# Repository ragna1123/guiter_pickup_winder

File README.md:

# ピックアップ製造計画

## ワインダー

## ピックアップボビン&カバー

### ラインナップ

- TELECASTER
- JAZZMASTER
- P90

### 実装予定

- A90
- STRATCASTER

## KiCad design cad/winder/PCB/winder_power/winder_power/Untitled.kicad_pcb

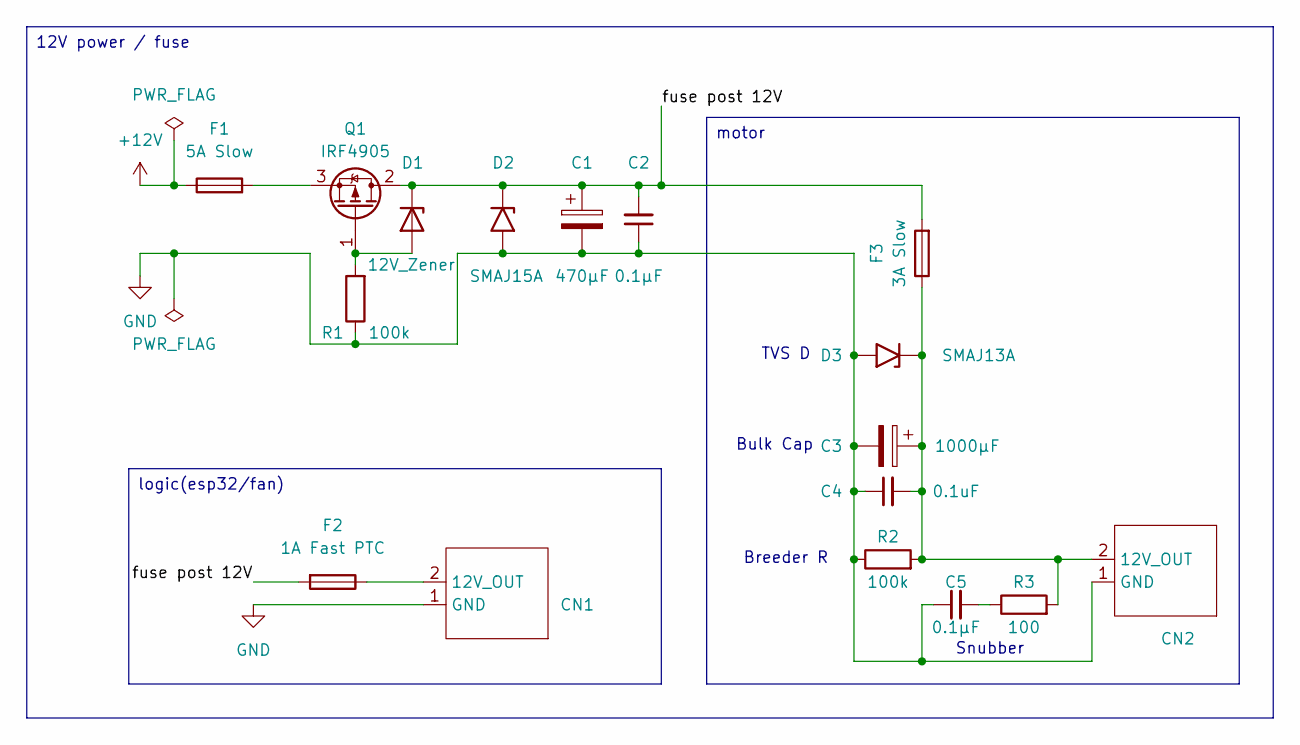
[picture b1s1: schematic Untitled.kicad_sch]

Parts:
C1: 470µF; CP_Radial_D10.0mm_P5.00mm
C2, C5: 0.1µF; C_1206_3216Metric_Pad1.33x1.80mm_HandSolder
C3: 1000µF; CP_Radial_D13.0mm_P5.00mm
C4: 0.1uF; C_1206_3216Metric_Pad1.33x1.80mm_HandSolder
CN1: JST_XH_B2B-XH-AM_1x02_P2.50mm_Vertical
CN2: JST_VH_B2P-VH-B_1x02_P3.96mm_Vertical
D1: 12V_Zener; TSOT-23_HandSoldering
D2: SMAJ15A; D_SMA
D3: SMAJ13A; D_SMA
F1: 5A Slow; FuseHolder_Blade_ATO_Littelfuse_FLR_178.6165
F2: 1A Fast PTC; Fuse_Bourns_MF-RHT070
F3: 3A Slow; FuseHolder_Blade_ATO_Littelfuse_FLR_178.6165
Q1: IRF4905; TO-220-3_Vertical
R1, R2: 100k; R_1206_3216Metric_Pad1.30x1.75mm_HandSolder
R3: 100; R_1206_3216Metric_Pad1.30x1.75mm_HandSolder

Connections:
+12V: F1.1; also elsewhere on the board
/fuse post 12V: C1.1, C2.2, D1.1 (K), D2.1 (A1), F2.2, F3.2, Q1.2 (D)
GND: C1.2, C2.1, C3.2, C4.1, C5.1, CN1.1 (GND), CN2.1 (GND), D2.2 (A2), D3.2 (A2), R1.1, R2.1; also elsewhere on the board
unnamed: C5.2, R3.1
unnamed: CN1.2 (12V_OUT), F2.1
unnamed: C3.1, C4.2, CN2.2 (12V_OUT), D3.1 (A1), F3.1, R2.2, R3.2
unnamed: D1.2 (A), Q1.1 (G), R1.2
unnamed: F1.2, Q1.3 (S)

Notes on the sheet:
Bulk Cap
Breeder R
TVS D
Snubber
logic(esp32/fan)
12V power / fuse
motor

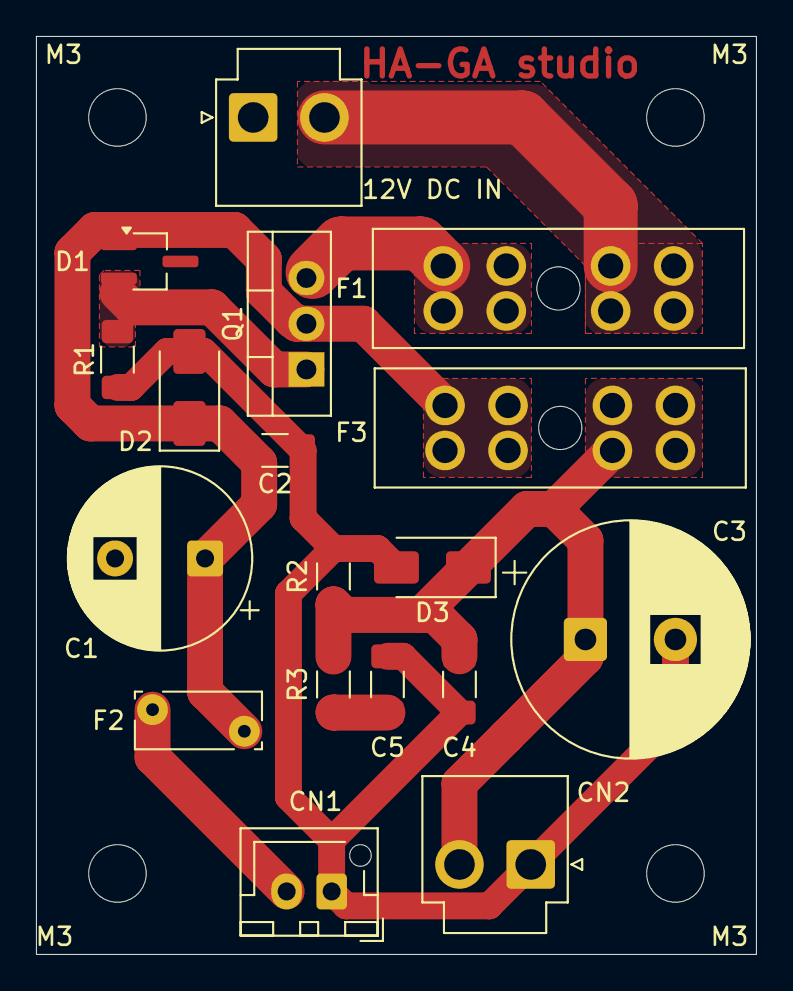
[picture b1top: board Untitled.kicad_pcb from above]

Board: 2 copper layers, 40.0 x 51.0 mm, 22 parts (0 on the bottom side), 8 nets.

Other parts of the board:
12V DC IN: JST_VH_B2P-VH-B_1x02_P3.96mm_Vertical
M3, M3#2, M3#3, M3#4: MountingHole_3.2mm_M3

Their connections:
+12V: 12V DC IN.2; also elsewhere on the board
GND: 12V DC IN.1; also elsewhere on the board

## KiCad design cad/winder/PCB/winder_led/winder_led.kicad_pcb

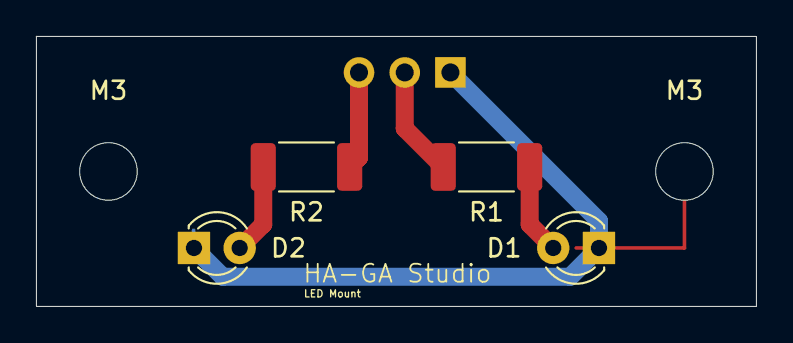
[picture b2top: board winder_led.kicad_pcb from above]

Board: 2 copper layers, 40.0 x 15.0 mm, 7 parts (1 on the bottom side), 5 nets.

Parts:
D1, D2: LED; LED_D3.0mm_FlatTop
J1: PinHeader_1x03_P2.54mm_Vertical
M3, M3#2: MountingHole_3.2mm_M3
R1, R2: R_Small; R_2010_5025Metric_Pad1.40x2.65mm_HandSolder

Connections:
/GPIO4: J1.2, R1.1
/GPIO5: J1.3, R2.1
GND: D1.1 (K), D2.1 (K), J1.1
unnamed: D1.2 (A), R1.2
unnamed: D2.2 (A), R2.2

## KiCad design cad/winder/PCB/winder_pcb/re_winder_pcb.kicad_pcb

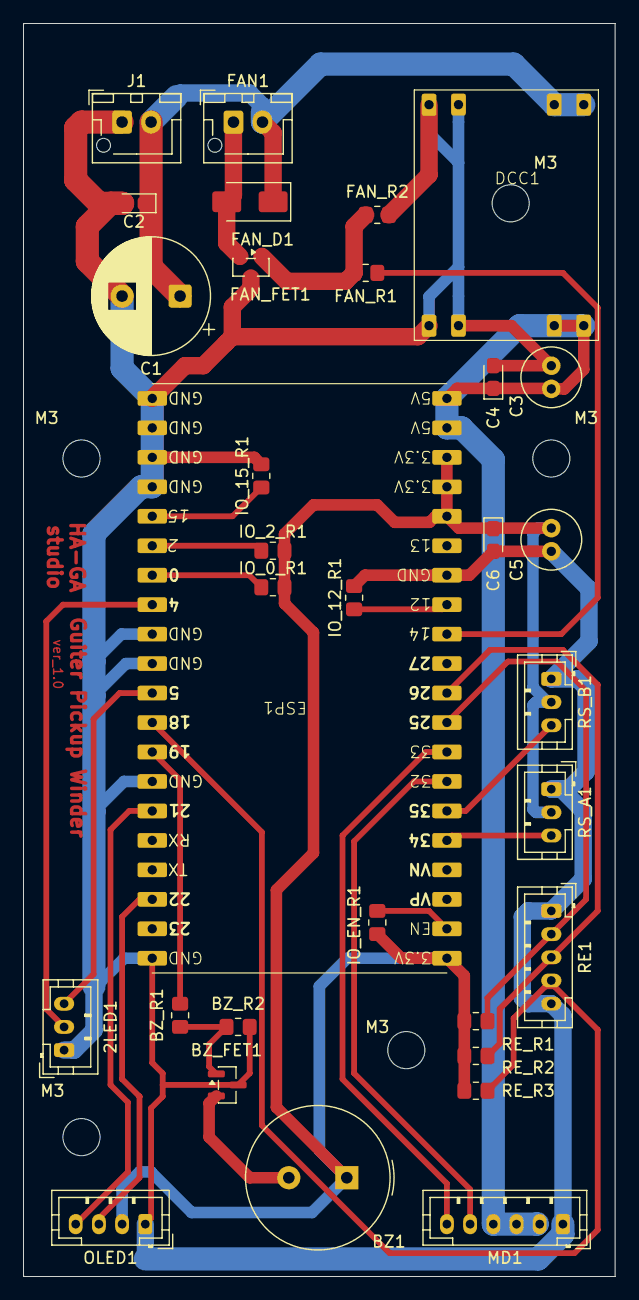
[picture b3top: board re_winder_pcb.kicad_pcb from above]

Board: 2 copper layers, 51.0 x 108.0 mm, 37 parts (0 on the bottom side), 26 nets.

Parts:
2LED1: LED; JST_PH_B3B-PH-K_1x03_P2.00mm_Vertical
BZ1: Buzzer; Buzzer_TDK_PS1240P02BT_D12.2mm_H6.5mm
BZ_FET1: AO3400A; SOT-23
BZ_R1: 100_R; R_0805_2012Metric_Pad1.20x1.40mm_HandSolder
BZ_R2: 100K_R; R_0805_2012Metric_Pad1.20x1.40mm_HandSolder
C1: 470uF; CP_Radial_D10.0mm_P5.00mm
C2, C4, C6: 0.1uF; CP_EIA-2012-12_Kemet-R_HandSolder
C3: 47uF; C_Radial_D5.0mm_H11.0mm_P2.00mm
C5: 10uF; C_Radial_D5.0mm_H11.0mm_P2.00mm
DCC1: DC_DW; MP1584EN_DCDC_Converter
ESP1: ESP32_Freenove_Socket
FAN1: 12V_Fan; JST_XH_B2B-XH-AM_1x02_P2.50mm_Vertical
FAN_D1: SS14; D_SMA
FAN_FET1: AO3400A; SOT-23
FAN_R1: 100_R; R_0805_2012Metric_Pad1.20x1.40mm_HandSolder
FAN_R2: 100K_R; R_0805_2012Metric_Pad1.20x1.40mm_HandSolder
IO_0_R1, IO_2_R1, IO_12_R1, IO_15_R1: 10K_R; R_0805_2012Metric_Pad1.20x1.40mm_HandSolder
IO_EN_R1: 10K_R; R_0805_2012Metric_Pad1.20x1.40mm_HandSolder
J1: 12V_IN; JST_XH_B2B-XH-AM_1x02_P2.50mm_Vertical
M3, M3#2, M3#3, M3#4, M3#5: MountingHole_3.2mm_M3
MD1: JST_PH_B6B-PH-K_1x06_P2.00mm_Vertical
OLED1: JST_PH_B4B-PH-K_1x04_P2.00mm_Vertical
RE1: RotaryEncoder_Switch; JST_PH_B5B-PH-K_1x05_P2.00mm_Vertical
RE_R1, RE_R2, RE_R3: 10K_R; R_0805_2012Metric_Pad1.20x1.40mm_HandSolder
RS_A1: JST_PH_B3B-PH-K_1x03_P2.00mm_Vertical
RS_B1: JST_PH_B3B-PH-K_1x03_P2.00mm_Vertical

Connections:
+5V: C3.1, C4.1, DCC1.4 (V_OUT+), ESP1.2 (5V), MD1.2 (VCC), MD1.3 (R_EN), MD1.4 (L_EN)
+12V: C1.1, C2.1, DCC1.2 (V_IN+), FAN1.2 (+), FAN_D1.1 (K), J1.2
/+3.3V: BZ1.1 (+), C5.1, C6.1, ESP1.3 (3.3V), IO_0_R1.2, IO_2_R1.2, IO_EN_R1.2, OLED1.2 (VCC), RE_R1.1, RE_R2.2, RE_R3.2, RS_A1.2 (VCC), RS_B1.2 (VCC)
/GPIO_4: 2LED1.2 (FW_LED), ESP1.25 (4)
/GPIO_5: 2LED1.3 (REV_LED), ESP1.24 (5)
/GPIO_14: ESP1.12 (14), FAN_R1.1
/GPIO_18: ESP1.23 (18), RE1.4 (S1), RE_R3.1
/GPIO_19: BZ_R1.2, ESP1.22 (19)
/GPIO_21: ESP1.21 (21/I2C(SDA)), OLED1.4 (SDA)
/GPIO_22: ESP1.20 (22/I2C(SCL)), OLED1.3 (SCL)
/GPIO_25: ESP1.9 (25), RE1.2 (A), RE_R1.2
/GPIO_26: ESP1.10 (26), RE1.3 (B), RE_R2.1
/GPIO_32: ESP1.7 (32), MD1.5 (R_PWM)
/GPIO_33: ESP1.8 (33), MD1.6 (L_PWM)
/GPIO_34: ESP1.5 (34), RS_A1.3 (DO)
/GPIO_35: ESP1.6 (35), RS_B1.3 (DO)
GND: 2LED1.1 (GND), BZ_FET1.3 (D), BZ_R2.1, C1.2, C2.2, C3.2, C4.2, C5.2, C6.2, DCC1.1 (V_IN-), DCC1.3 (V_OUT-), ESP1.1 (GND), FAN_FET1.3 (D), FAN_R2.2, IO_12_R1.2, IO_15_R1.2, J1.1, MD1.1 (GND), OLED1.1 (GND), RE1.1 (C), RE1.5 (S2), RS_A1.1 (GND), RS_B1.1 (GND)
unnamed: BZ1.2 (-), BZ_FET1.2 (S)
unnamed: BZ_FET1.1 (G), BZ_R1.1, BZ_R2.2
unnamed: ESP1.26 (0/Boot), IO_0_R1.1
unnamed: ESP1.27 (2), IO_2_R1.1
unnamed: ESP1.13 (12), IO_12_R1.1
unnamed: ESP1.28 (15), IO_15_R1.1
unnamed: ESP1.4 (EN), IO_EN_R1.1
unnamed: FAN1.1 (-), FAN_D1.2 (A), FAN_FET1.2 (S)
unnamed: FAN_FET1.1 (G), FAN_R1.2, FAN_R2.1

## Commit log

2025-08-28 雛形生成
2025-08-30 CAD作成
2025-08-30 ブランチ切り替え
2025-08-30 画像の追加
2025-09-14 pick_upパーツを追加
2025-09-14 ジャズマスターパーツを追加
2025-09-14 doc整理
2025-09-17 v2モデルをアップ
2025-09-22 チャッキの抑え機構追加
2025-09-24 docにlcd_menuを追加
2025-09-27 test modelの追加
2025-10-12 筐体を作成
2025-10-27 基盤周りのアップ
2025-12-04 パワー基盤の作成完了
2026-01-06 パーツリストMDを作成
2026-01-14 パーツリスト出し
2026-06-18 Add consolidated winder specs
2026-06-18 Fix winder asset naming and BOM units
